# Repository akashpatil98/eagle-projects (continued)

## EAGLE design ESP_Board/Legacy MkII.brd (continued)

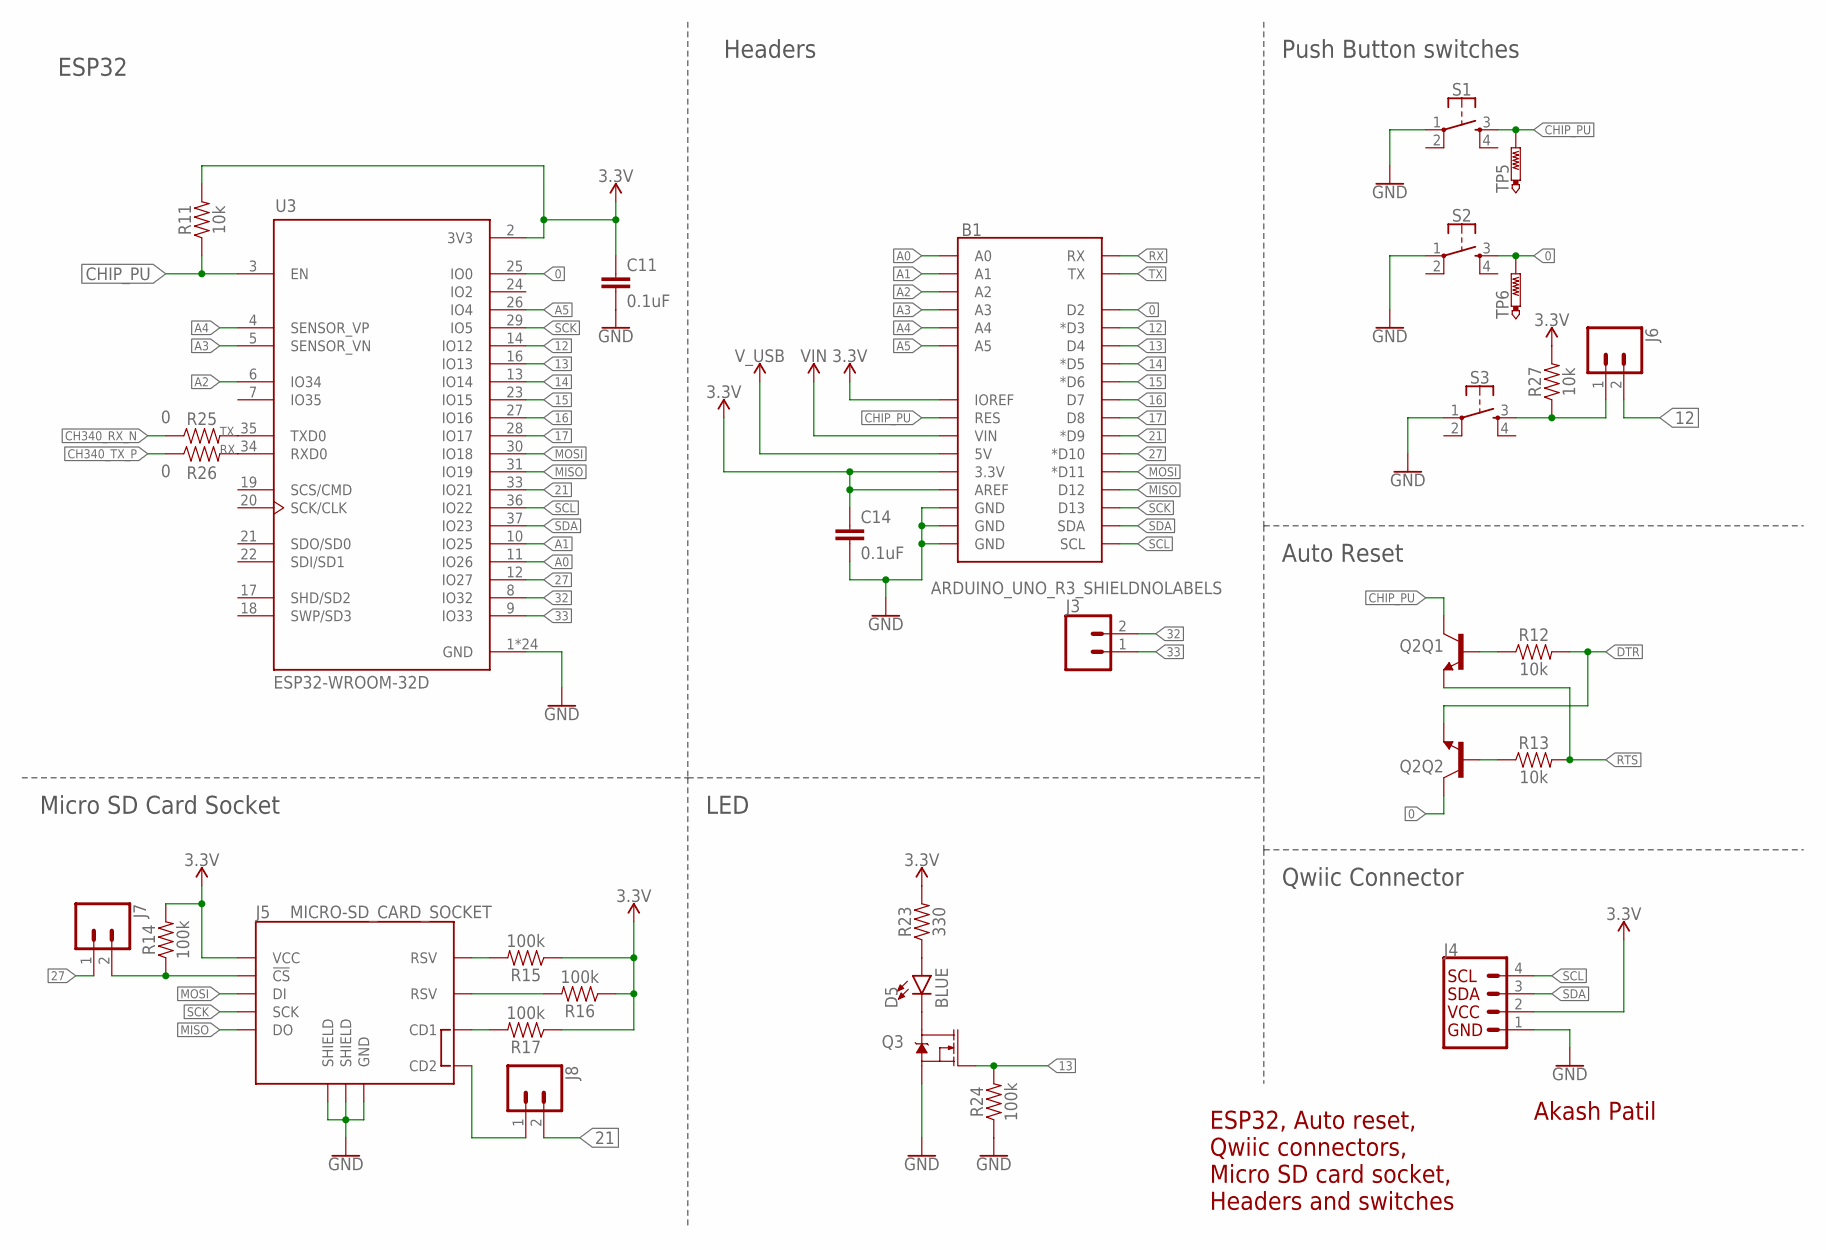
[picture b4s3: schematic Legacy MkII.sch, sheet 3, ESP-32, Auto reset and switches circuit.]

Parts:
B1: ARDUINO_UNO_R3_SHIELDNOLABELS; UNO_R3_SHIELD_NOLABELS
C11, C14: 0.1uF; 0603
D5: BLUE; LED-0603
J3: CONN_021X02_NO_SILK; 1X02_NO_SILK
J4: QWIIC_CONNECTORJS-1MM; 1X04_1MM_RA
J5: MICRO-SD_CARD_SOCKET; MICRO-SD-SOCKET
J6, J7, J8: CONN_02; 1X02
Q2: TRANS_NPN_DUAL-MBT3904DW1T1; SC70-6
Q3: 220mA/50V/3.5Ω; SOT23-3
R11, R12, R13, R27: 10k; 0603
R14, R15, R16, R17, R24: 100k; 0603
R23: 330; 0603
R25, R26: 0; 0603
S1, S2, S3: MOMENTARY-SWITCH-SPST-2-SMD-4.6X2.8MM; TACTILE_SWITCH_SMD_4.6X2.8MM
TP5, TP6: PTR1B1,27; B1,27
U3: ESP32-WROOM-32D; MODULE_ESP32-WROOM-32D

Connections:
0: B1.D2, Q2.6 (C), S2.3, TP6.TP, U3.25 (IO0)
3.3V: B1.3.3V, B1.AREF, B1.IOREF, C11.1, C14.1, J4.2 (VCC), J5.VCC, R11.2, R14.2, R15.1, R16.1, R17.1, R23.2, R27.2, U3.2 (3V3); also elsewhere on the board
12: B1.D3 (*D3), J6.2, U3.14 (IO12)
13: B1.D4, Q3.1 (G), R24.2, U3.16 (IO13)
14: B1.D5 (*D5), U3.13 (IO14)
15: B1.D6 (*D6), U3.23 (IO15)
16: B1.D7, U3.27 (IO16)
17: B1.D8, U3.28 (IO17)
21: B1.D9 (*D9), J8.2, U3.33 (IO21)
27: B1.D10 (*D10), J7.1, U3.12 (IO27)
32: J3.2, U3.8 (IO32)
33: J3.1, U3.9 (IO33)
A0: B1.A0, U3.11 (IO26)
A1: B1.A1, U3.10 (IO25)
A2: B1.A2, U3.6 (IO34)
A3: B1.A3, U3.5 (SENSOR_VN)
A4: B1.A4, U3.4 (SENSOR_VP)
A5: B1.A5, U3.26 (IO4)
CH340_RX_N: R25.1; also elsewhere on the board
CH340_TX_P: R26.1; also elsewhere on the board
CHIP_PU: B1.RES, Q2.3 (C), R11.1, S1.3, TP5.TP, U3.3 (EN)
DTR: Q2.1 (E), R12.2; also elsewhere on the board
GND: B1.GND@0 (GND), B1.GND@1 (GND), B1.GND@2 (GND), C11.2, C14.2, J4.1 (GND), J5.GND, J5.GND1 (SHIELD), J5.GND3 (SHIELD), Q3.2 (S), R24.1, S1.1, S2.1, S3.1, U3.1 (GND), U3.15 (GND), U3.38 (GND), U3.39_1 (GND), U3.39_2 (GND), U3.39_3 (GND), U3.39_4 (GND), U3.39_5 (GND), U3.39_6 (GND), U3.39_7 (GND), U3.39_8 (GND), U3.39_9 (GND), U3.39_10 (GND), U3.39_11 (GND), U3.39_12 (GND), U3.39_13 (GND), U3.39_14 (GND), U3.39_15 (GND), U3.39_16 (GND), U3.39_17 (GND), U3.39_18 (GND), U3.39_19 (GND), U3.39_20 (GND), U3.39_21 (GND); also elsewhere on the board
MISO: B1.D12, J5.DO, U3.31 (IO19)
MOSI: B1.D11 (*D11), J5.DI, U3.30 (IO18)
unnamed: J5.CD2, J8.1
unnamed: J5.CS (!CS), J7.2, R14.1
unnamed: D5.A, R23.1
unnamed: Q2.5 (B), R12.1
unnamed: Q2.2 (B), R13.1
unnamed: J5.RSV1 (RSV), R15.2
unnamed: D5.C, Q3.3 (D)
unnamed: J5.RSV2 (RSV), R16.2
unnamed: J5.CD1, R17.2
unnamed: J6.1, R27.1, S3.3
RTS: Q2.4 (E), R13.2; also elsewhere on the board
RX: B1.RX, R26.2, U3.34 (RXD0)
SCK: B1.D13, J5.SCLK (SCK), U3.29 (IO5)
SCL: B1.SCL, J4.4 (SCL), U3.36 (IO22)
SDA: B1.SDA, J4.3 (SDA), U3.37 (IO23)
TX: B1.TX, R25.2, U3.35 (TXD0)
VIN: B1.VIN; also elsewhere on the board
V_USB: B1.5V; also elsewhere on the board

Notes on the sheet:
Akash Patil
ESP32, Auto reset, Qwiic connectors, Micro SD card socket, Headers and switches
Auto Reset
Push Button switches
ESP32
LED
Qwiic Connector
Headers
Micro SD Card Socket

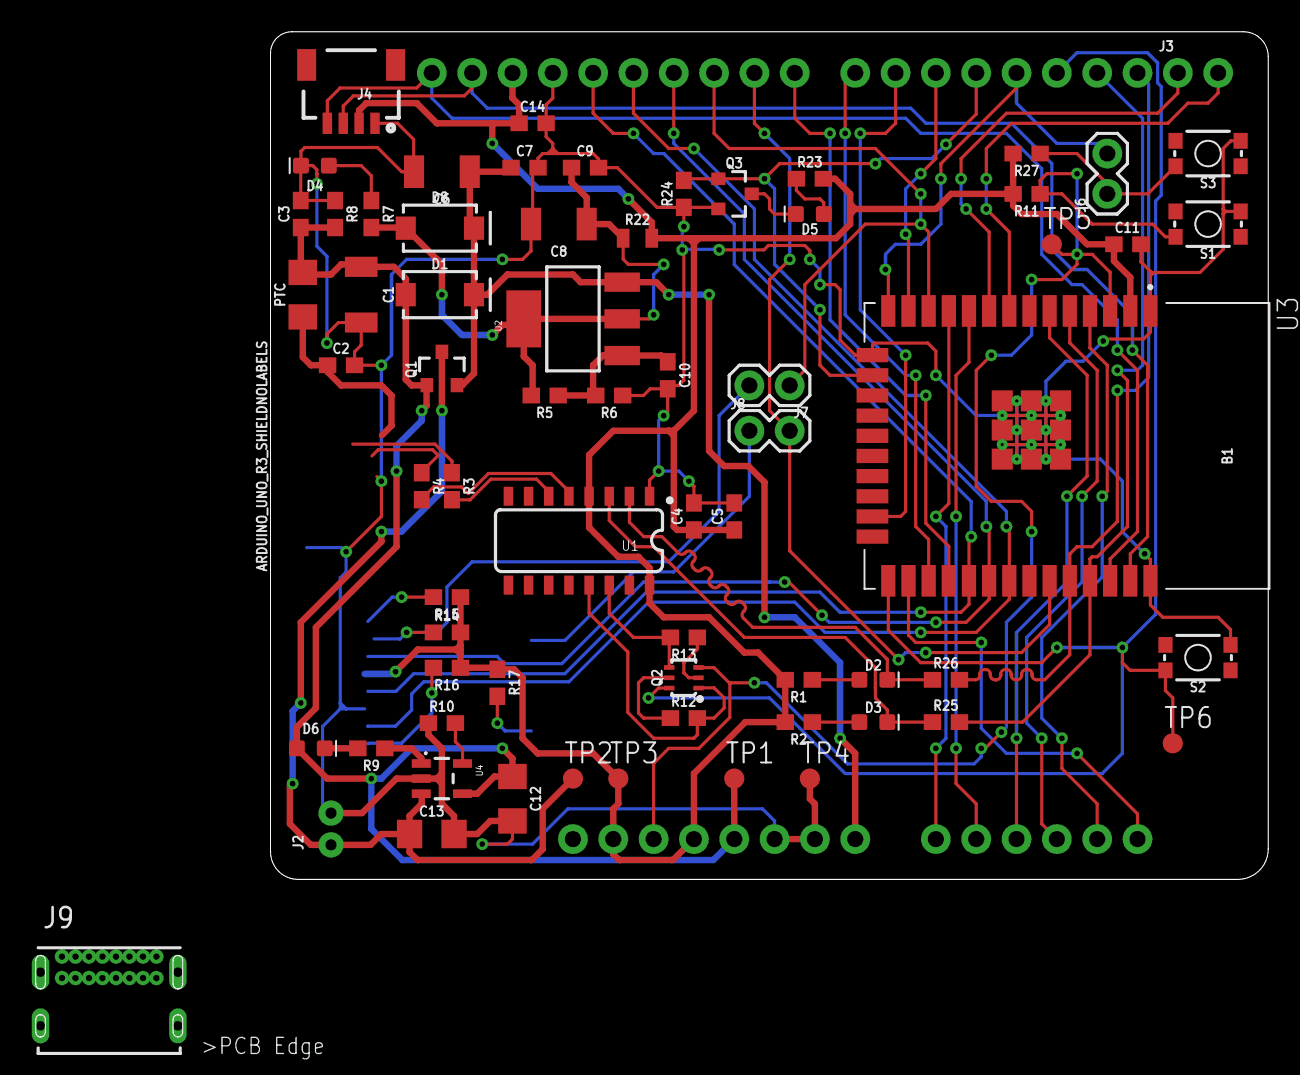
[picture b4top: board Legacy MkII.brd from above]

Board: 2 copper layers, 77.6 x 63.3 mm, 70 parts (1 on the bottom side), 58 nets.

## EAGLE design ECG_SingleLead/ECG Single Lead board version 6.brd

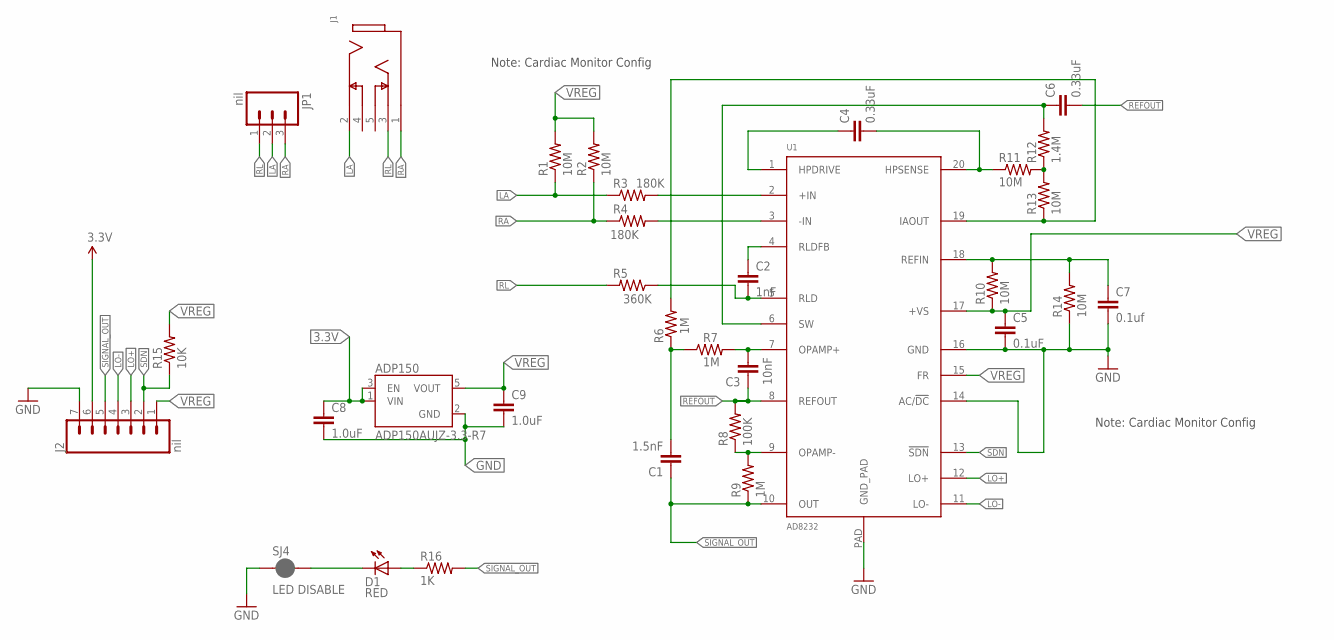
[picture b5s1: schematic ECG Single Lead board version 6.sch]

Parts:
ADP150: ADP150AUJZ-3.3-R7; SOT95P280X100-5N
C1: 1.5nF; 0603-CAP
C2: 1nF; 0603-CAP
C3: 10nF; 0603-CAP
C4, C6: 0.33uF; 0805
C5: 0.1uF; 0603-CAP
C7: 0.1uf; 0603-CAP
C8, C9: 1.0uF; 0603
D1: RED; LED-0603
J1: 35RASMT4BHNTRX; SWITCHCRAFT_35RASMT4BHNTRX
J2: nil; 1X07
JP1: nil; 1X03
R1, R2, R10, R11, R13, R14: 10M; 0603-RES
R3, R4: 180K; 0603-RES
R5: 360K; 0603-RES
R6, R7, R9: 1M; 0603-RES
R8: 100K; 0603-RES
R12: 1.4M; 0603-RES
R15: 10K; 0603-RES
R16: 1K; 0603-RES
SJ4: LED DISABLE; SMT-JUMPER_2_NC_PASTE_SILK
U1: AD8232; LFCSP_20

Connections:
3.3V: ADP150.1 (VIN), ADP150.3 (EN), C8.1, J2.6
GND: ADP150.2 (GND), C5.2, C7.2, C8.2, C9.2, J2.7, R14.1, SJ4.1, U1.14 (AC/!DC), U1.16 (GND), U1.PAD (GND_PAD)
LA: J1.2, JP1.2, R1.1, R3.1
LO+: J2.3, U1.12 (LO+)
LO-: J2.4, U1.11 (LO-)
unnamed: R3.2, U1.2 (+IN)
unnamed: R4.2, U1.3 (-IN)
unnamed: C3.2, R7.2, U1.7 (OPAMP+)
unnamed: C4.2, R11.1, U1.20 (HPSENSE)
unnamed: C7.1, R10.2, R14.2, U1.18 (REFIN)
unnamed: D1.A, R16.1
unnamed: R8.1, R9.2, U1.9 (OPAMP-)
unnamed: R6.2, R13.1, U1.19 (IAOUT)
unnamed: C1.2, R6.1, R7.1
unnamed: D1.C, SJ4.2
unnamed: C4.1, U1.1 (HPDRIVE)
unnamed: R11.2, R12.1, R13.2
unnamed: C6.1, R12.2, U1.6 (SW)
unnamed: C2.1, U1.4 (RLDFB)
unnamed: C2.2, R5.1, U1.5 (RLD)
RA: J1.1, JP1.3, R2.1, R4.1
REFOUT: C3.1, C6.2, R8.2, U1.8 (REFOUT)
RL: J1.3, JP1.1, R5.2
SDN: J2.2, R15.1, U1.13 (!SDN)
SIGNAL_OUT: C1.1, J2.5, R9.1, R16.2, U1.10 (OUT)
VREG: ADP150.5 (VOUT), C5.1, C9.1, J2.1, R1.2, R2.2, R10.1, R15.2, U1.15 (FR), U1.17 (+VS)

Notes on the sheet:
Note: Cardiac Monitor Config

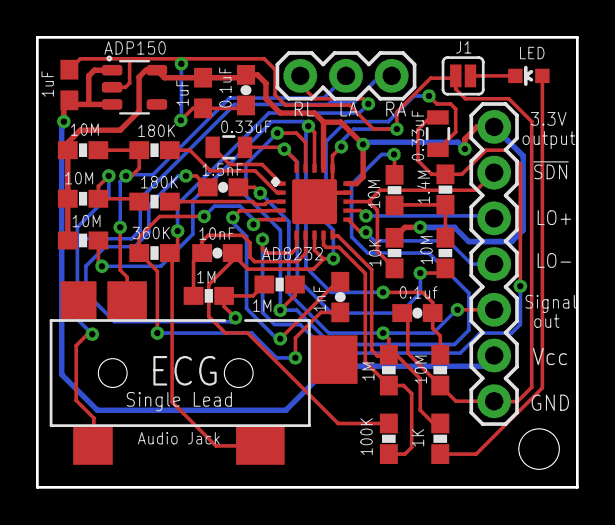
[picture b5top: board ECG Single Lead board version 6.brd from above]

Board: 2 copper layers, 30.0 x 25.0 mm, 32 parts (0 on the bottom side), 26 nets.

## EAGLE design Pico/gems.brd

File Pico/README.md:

## This folder contains the design files for Pico development kit

### The design was created using Autodesk Eagle.

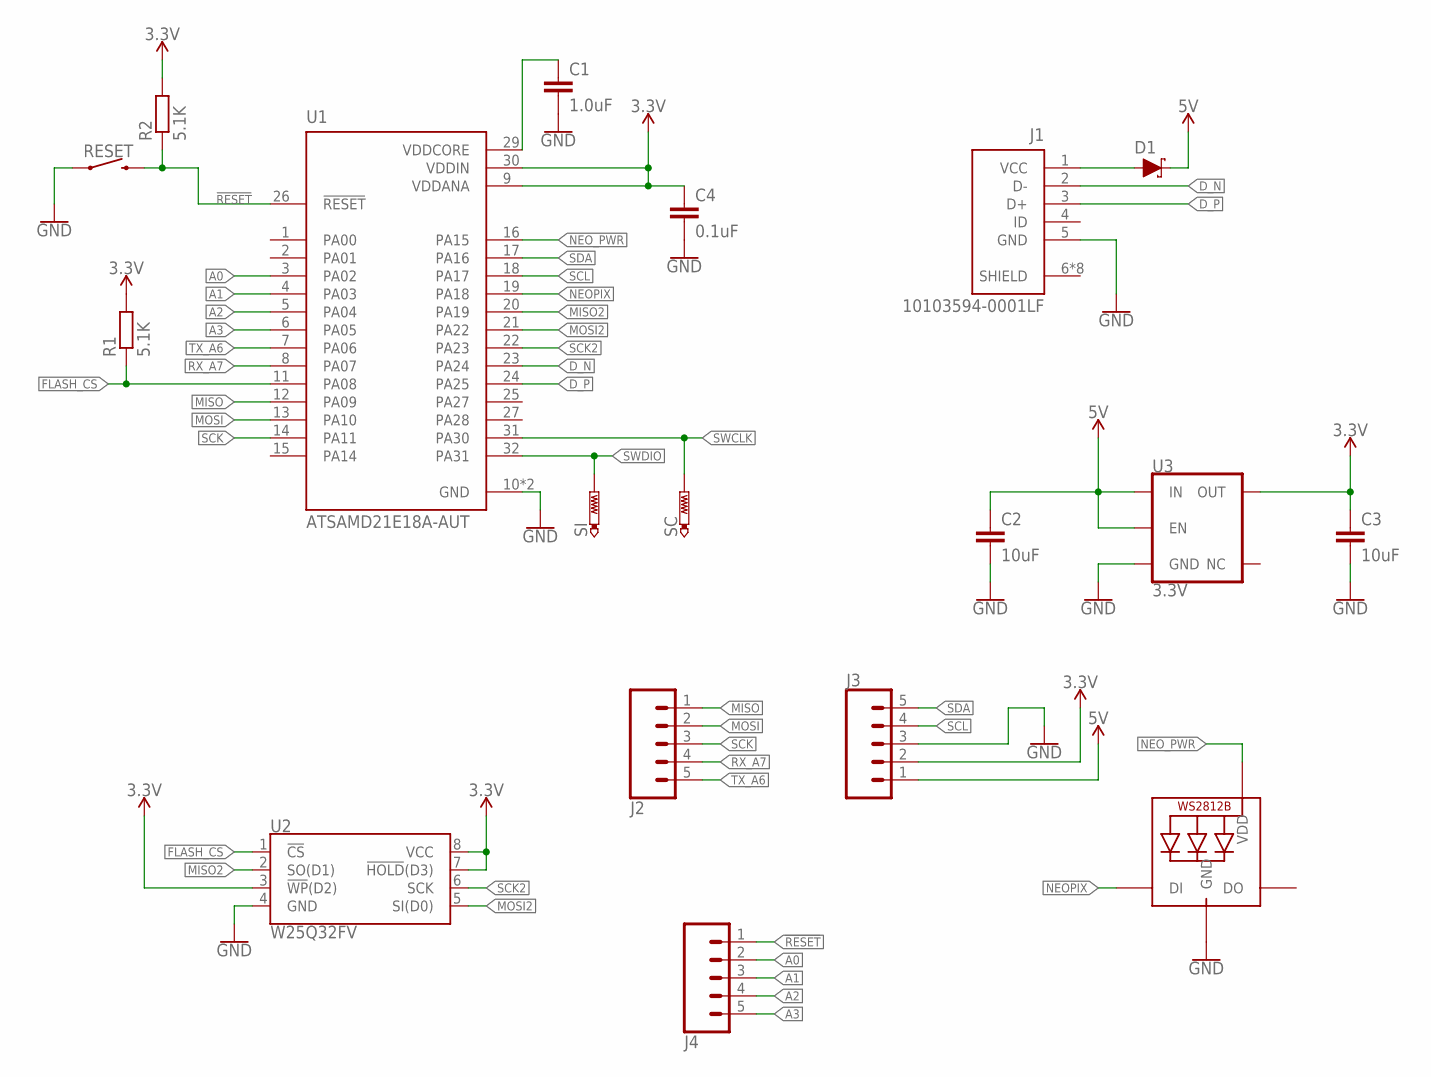
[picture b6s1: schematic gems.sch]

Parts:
C1: 1.0uF; 0402
C2, C3: 10uF; 0603
C4: 0.1uF; 0402
D1: 0.5A/40V/420mV; SOD-323
J1: 10103594-0001LF; AMPHENOL_10103594-0001LF
J2, J3, J4: CONN_05; 1X05
LED: WS2812B_SK6805_1515; SK6805_1515
R1, R2: 5.1K; R0402
RESET: MOMENTARY-SWITCH-SPST-SMD-4.6X2.8MM; TACTILE_SWITCH_SMD_4.6X2.8MM
SC: PTR1TP08R; TP08R
SI: PTR1TP08R; TP08R
U1: ATSAMD21E18A-AUT; QFP80P900X900X120-32N
U2: W25Q32FV; SOIC-8
U3: 3.3V; SOT23-5

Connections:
3.3V: C3.1, C4.1, J3.2, R1.2, R2.2, U1.9 (VDDANA), U1.30 (VDDIN), U2.3 (!WP!(D2)), U2.7 (!HOLD!(D3)), U2.8 (VCC), U3.5 (OUT)
5V: C2.1, D1.C, J3.1, U3.1 (IN), U3.3 (EN)
!RESET!: J4.1, R2.1, RESET.3 (2), RESET.4 (2), U1.26 (!RESET)
A0: J4.2, U1.3 (PA02)
A1: J4.3, U1.4 (PA03)
A2: J4.4, U1.5 (PA04)
A3: J4.5, U1.6 (PA05)
D_N: J1.2 (D-), U1.23 (PA24)
D_P: J1.3 (D+), U1.24 (PA25)
FLASH_CS: R1.1, U1.11 (PA08), U2.1 (!CS!)
GND: C1.2, C2.2, C3.2, C4.2, J1.5 (GND), J3.3, LED.4 (GND), RESET.1, RESET.2 (1), U1.10 (GND), U1.28 (GND), U2.4 (GND), U3.2 (GND)
MISO: J2.1, U1.12 (PA09)
MISO2: U1.20 (PA19), U2.2 (SO(D1))
MOSI: J2.2, U1.13 (PA10)
MOSI2: U1.21 (PA22), U2.5 (SI(D0))
unnamed: C1.1, U1.29 (VDDCORE)
unnamed: D1.A, J1.1 (VCC)
NEOPIX: LED.1 (DI), U1.19 (PA18)
NEO_PWR: LED.2 (VDD), U1.16 (PA15)
RX_A7: J2.4, U1.8 (PA07)
SCK: J2.3, U1.14 (PA11)
SCK2: U1.22 (PA23), U2.6 (SCK)
SCL: J3.4, U1.18 (PA17)
SDA: J3.5, U1.17 (PA16)
SWCLK: SC.TP, U1.31 (PA30)
SWDIO: SI.TP, U1.32 (PA31)
TX_A6: J2.5, U1.7 (PA06)

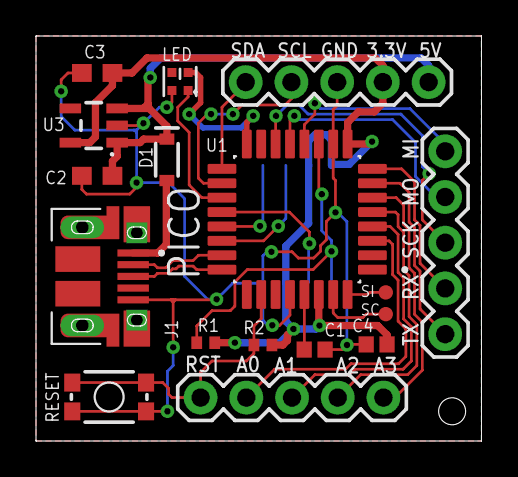
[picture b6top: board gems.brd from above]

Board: 2 copper layers, 24.8 x 22.5 mm, 18 parts (1 on the bottom side), 27 nets.

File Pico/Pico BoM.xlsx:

Qty | Value | MPN | Package | Parts | Description | Digikey PN | Loading
3 |  |  | 1X05 | J2, J3, J4 | Generic Header-pin footprint for 0.1 inch spaced/style header connections |  | DNP
1 | 0.1uF | CL05B104KP5NNNC | 0402 | C4 | CAP CER 0.1UF 10V X7R 0402 | 1276-1002-1-ND
1 | 0.5A/40V/420mV | PMEG3010BEA,115 | SOD-323 | D1 | DIODE SCHOTTKY 30V 1A SOD323 | 1727-5199-1-ND
1 | 1.0uF | CL05A105MP5NNNC | 0402 | C1 | CAP CER 1UF 10V X5R 0402 | 1276-1448-1-ND
1 | 10103594-0001LF | 10103594-0001LF | AMPHENOL_10103594-0001LF | J1 | CONN RCPT USB2.0 MICRO B SMD R/A | 609-4050-1-ND
2 | 10uF | LMK107BBJ106MALT | 0603 | C2, C3 | CAP CER 10UF 10V X5R 0603 | 587-3258-1-ND
1 | 3.3V | AP2112K-3.3TRG1 | SOT23-5 | U3 | IC REG LINEAR 3.3V 600MA SOT25 | AP2112K-3.3TRG1DICT-ND
2 | 5.1K | RMCF0402JT5K10 | 0402 | R1, R2 | RES 5.1K OHM 5% 1/16W 0402 | RMCF0402JT5K10CT-ND
1 | ATSAMD21E18A-AUT | ATSAMD21E18A-AUT | 32-TQFP | U1 | IC MCU 32BIT 256KB FLASH 32TQFP | ATSAMD21E18A-AUTCT-ND
1 | MOMENTARY-SWITCH-SPST-SMD-4.6X2.8MM | KMR221GLFS | TACTILE_SWITCH_SMD_4.6X2.8MM | RESET | SWITCH TACTILE SPST-NO 0.05A 32V | 401-1427-1-ND
1 | SK6805-E-J | 4492 | SK6805_1515 | LED | ADDRESS LED DISCRETE RGB 1=10 | 1528-4492-ND

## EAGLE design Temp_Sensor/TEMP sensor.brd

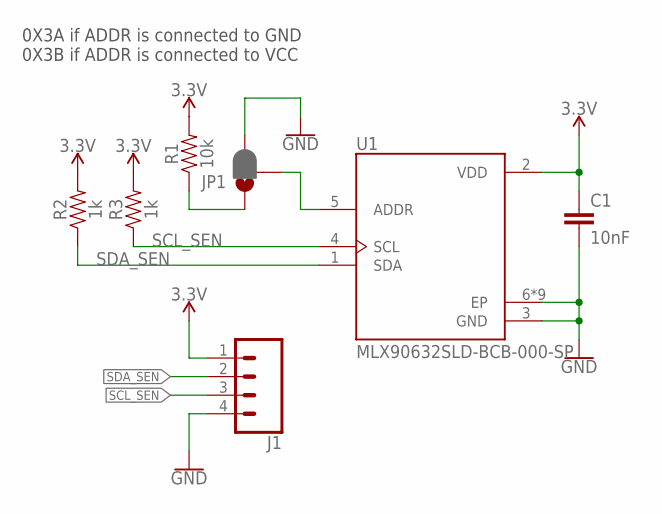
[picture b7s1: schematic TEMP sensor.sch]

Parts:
C1: 10nF; 0603
J1: CONN_04; 1X04
JP1: JUMPER-SMT_3_1-NC_PASTE_SILK; SMT-JUMPER_3_1-NC_PASTE_SILK
R1: 10k; 0603
R2, R3: 1k; 0603
U1: MLX90632SLD-BCB-000-SP; XDCR_MLX90632SLD-BCB-000-SP

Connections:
3.3V: C1.1, J1.1, R1.2, R2.2, R3.2, U1.2 (VDD)
GND: C1.2, J1.4, JP1.3, U1.3 (GND), U1.6 (EP), U1.P$1 (EP), U1.P$2 (EP), U1.P$3 (EP), U1.P$4 (EP), U1.P$5 (EP), U1.P$6 (EP), U1.P$7 (EP), U1.P$8 (EP)
unnamed: JP1.2, U1.5 (ADDR)
unnamed: JP1.1, R1.1
SCL_SEN: J1.3, R3.1, U1.4 (SCL)
SDA_SEN: J1.2, R2.1, U1.1 (SDA)

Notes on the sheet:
0X3A if ADDR is connected to GND 0X3B if ADDR is connected to VCC

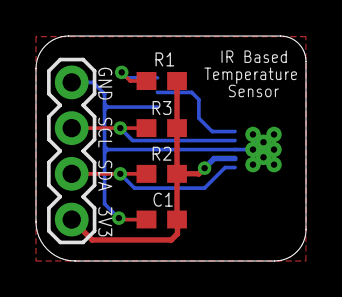
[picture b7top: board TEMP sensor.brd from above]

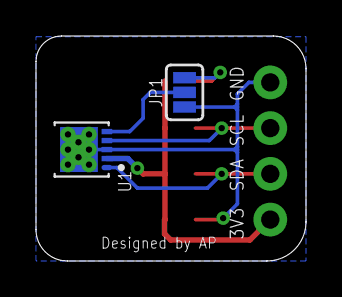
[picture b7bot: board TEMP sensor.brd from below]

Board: 2 copper layers, 15.0 x 12.5 mm, 7 parts (2 on the bottom side), 6 nets.

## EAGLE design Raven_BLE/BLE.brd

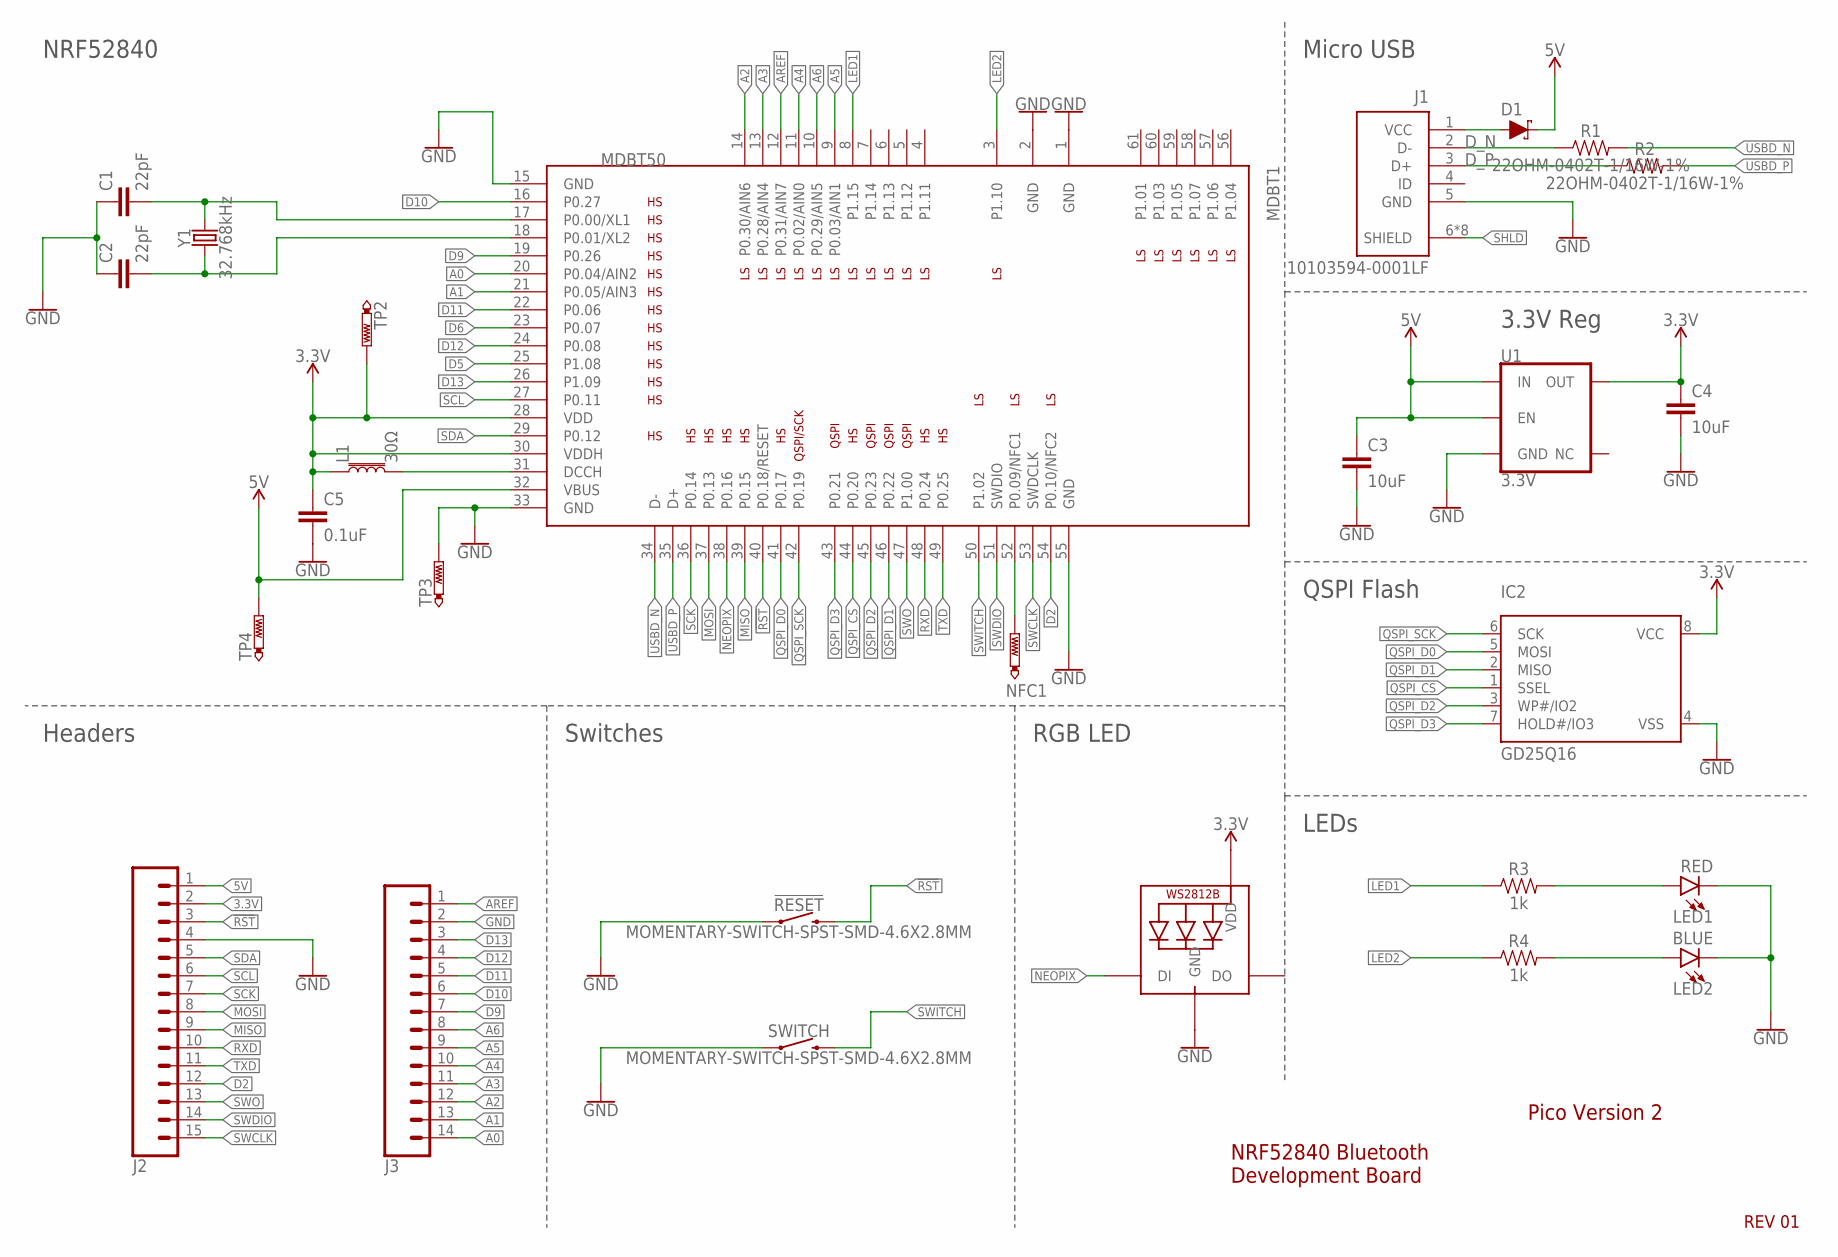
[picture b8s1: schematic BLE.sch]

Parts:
!RESET!: MOMENTARY-SWITCH-SPST-SMD-4.6X2.8MM; TACTILE_SWITCH_SMD_4.6X2.8MM
C1, C2: 22pF; 0402-TIGHT
C3, C4: 10uF; 0603
C5: 0.1uF; 0402-TIGHT
D1: 0.5A/40V/420mV; SOD-323
IC2: GD25Q16; USON8
J1: 10103594-0001LF; AMPHENOL_10103594-0001LF
J2: CONN_15; 1X15
J3: CONN_14; 1X14
L1: 30Ω; 0402-TIGHT
LED1: RED; LED-0603
LED2: BLUE; LED-0603
MDBT1: MDBT50
NFC1: PTR1TP10R; TP10R
R1, R2: 22OHM-0402T-1/16W-1%; 0402-TIGHT
R3, R4: 1k; 0402-TIGHT
RGB_LED: WS2812B_SK6805_1515; SK6805_1515
SWITCH: MOMENTARY-SWITCH-SPST-SMD-4.6X2.8MM; TACTILE_SWITCH_SMD_4.6X2.8MM
TP2, TP3, TP4: PTR1TP07R; TP07R
U1: 3.3V; SOT23-5
Y1: 32.768kHz; CRYSTAL-SMD-3.2X1.5MM

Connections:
3.3V: C4.1, C5.1, IC2.8 (VCC), J2.2, L1.1, MDBT1.28 (VDD), MDBT1.30 (VDDH), RGB_LED.2 (VDD), TP2.TP, U1.5 (OUT)
5V: C3.1, D1.C, J2.1, MDBT1.32 (VBUS), TP4.TP, U1.1 (IN), U1.3 (EN)
!RST!: !RESET!.3 (2), !RESET!.4 (2), J2.3, MDBT1.40 (P0.18/RESET)
A0: J3.14, MDBT1.20 (P0.04/AIN2)
A1: J3.13, MDBT1.21 (P0.05/AIN3)
A2: J3.12, MDBT1.14 (P0.30/AIN6)
A3: J3.11, MDBT1.13 (P0.28/AIN4)
A4: J3.10, MDBT1.11 (P0.02/AIN0)
A5: J3.9, MDBT1.9 (P0.03/AIN1)
A6: J3.8, MDBT1.10 (P0.29/AIN5)
AREF: J3.1, MDBT1.12 (P0.31/AIN7)
D2: J2.12, MDBT1.54 (P0.10/NFC2)
D5: MDBT1.25 (P1.08)
D6: MDBT1.23 (P0.07)
D9: J3.7, MDBT1.19 (P0.26)
D10: J3.6, MDBT1.16 (P0.27)
D11: J3.5, MDBT1.22 (P0.06)
D12: J3.4, MDBT1.24 (P0.08)
D13: J3.3, MDBT1.26 (P1.09)
D_N: J1.2 (D-), R1.1
D_P: J1.3 (D+), R2.1
GND: !RESET!.1, !RESET!.2 (1), C1.1, C2.1, C3.2, C4.2, C5.2, IC2.4 (VSS), J1.5 (GND), J2.4, J3.2, LED1.C, LED2.C, MDBT1.1 (GND), MDBT1.2 (GND), MDBT1.15 (GND), MDBT1.33 (GND), MDBT1.55 (GND), RGB_LED.4 (GND), SWITCH.1, SWITCH.2 (1), TP3.TP, U1.2 (GND)
LED1: MDBT1.8 (P1.15), R3.1
LED2: MDBT1.3 (P1.10), R4.1
MISO: J2.9, MDBT1.39 (P0.15)
MOSI: J2.8, MDBT1.37 (P0.13)
unnamed: C1.2, MDBT1.17 (P0.00/XL1), Y1.P$2 (2)
unnamed: C2.2, MDBT1.18 (P0.01/XL2), Y1.P$1 (1)
unnamed: D1.A, J1.1 (VCC)
unnamed: MDBT1.52 (P0.09/NFC1), NFC1.TP
unnamed: L1.2, MDBT1.31 (DCCH)
unnamed: LED1.A, R3.2
unnamed: LED2.A, R4.2
NEOPIX: MDBT1.38 (P0.16), RGB_LED.1 (DI)
QSPI_CS: IC2.1 (SSEL), MDBT1.44 (P0.20)
QSPI_D0: IC2.5 (MOSI), MDBT1.41 (P0.17)
QSPI_D1: IC2.2 (MISO), MDBT1.46 (P0.22)
QSPI_D2: IC2.3 (WP#/IO2), MDBT1.45 (P0.23)
QSPI_D3: IC2.7 (HOLD#/IO3), MDBT1.43 (P0.21)
QSPI_SCK: IC2.6 (SCK), MDBT1.42 (P0.19)
RXD: J2.10, MDBT1.48 (P0.24)
SCK: J2.7, MDBT1.36 (P0.14)
SCL: J2.6, MDBT1.27 (P0.11)
SDA: J2.5, MDBT1.29 (P0.12)
SHLD: J1.6 (SHIELD), J1.7 (SHIELD), J1.8 (SHIELD), J1.9 (SHIELD), J1.10 (SHIELD), J1.11 (SHIELD), J1.S1 (SHIELD), J1.S2 (SHIELD)
SWCLK: J2.15, MDBT1.53 (SWDCLK)
SWDIO: J2.14, MDBT1.51 (SWDIO)
SWITCH: MDBT1.50 (P1.02), SWITCH.3 (2), SWITCH.4 (2)
SWO: J2.13, MDBT1.47 (P1.00)
TXD: J2.11, MDBT1.49 (P0.25)
USBD_N: MDBT1.34 (D-), R1.2
USBD_P: MDBT1.35 (D+), R2.2

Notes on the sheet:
NRF52840
Headers
Switches
RGB LED
LEDs
QSPI Flash
3.3V Reg
Micro USB
REV 01
NRF52840 Bluetooth Development Board
Pico Version 2

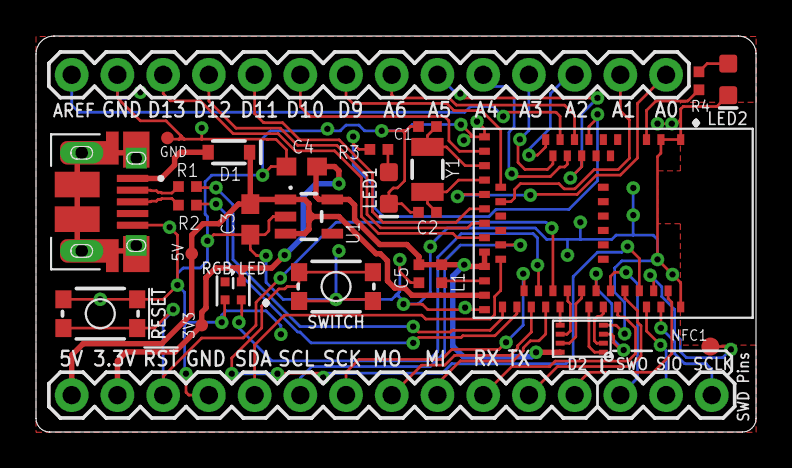
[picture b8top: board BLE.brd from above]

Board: 2 copper layers, 40.0 x 22.0 mm, 27 parts (0 on the bottom side), 50 nets.

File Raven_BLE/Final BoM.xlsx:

Column1 | Column2 | Column3 | Column4 | Column5 | Column6 | Column7
Part | Value | Device | Package | Description | Element14 | Digikey
!RESET! | MOMENTARY-SWITCH-SPST-SMD-4.6X2.8MM | MOMENTARY-SWITCH-SPST-SMD-4.6X2.8MM | TACTILE_SWITCH_SMD_4.6X2.8MM | Momentary Switch (Pushbutton) - SPST | Y
C1 | TBD (Load cap) | 22PF-0402T-16V-10% | 0402-TIGHT | Load caps for WCO | Y
C2 | TBD (Load cap) | 22PF-0402T-16V-10% | 0402-TIGHT | Load caps for WCO | Y
C3 | 10uF | 10UF-0603-6.3V-20% | 0603 | 10.0ÂµF ceramic capacitors | Y
C4 | 10uF | 10UF-0603-6.3V-20% | 0603 | 10.0ÂµF ceramic capacitors | Y
C5 | 0.1uF | 0.1UF-0402T-10V-10%-X7R | 0402-TIGHT | 0.1ÂµF ceramic capacitors | Y
D1 | 0.5A/40V/420mV | DIODE-SCHOTTKY-PMEG4005EJ | SOD-323 | Schottky diode | Y
IC2 | GD25Q16 | SPIFLASH_8PINUX | USON8 | SOIC8 SPI Flash
J1 | 10103594-0001LF | 10103594-0001LF | AMPHENOL_10103594-0001LF | USB - micro B USB 2.0 Receptacle Connector 5 Position Surface Mount, Right Angl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 | Y
LED1 | RED | LED-RED0603 | LED-0603 | Red SMD LED | Y
LED2 | BLUE | LED-BLUE0603 | LED-0603 | Blue SMD LED | Y
Module | MDBT50Q | MDBT50Q | MDBT50 | Raytac Corporation
R1 | 22OHM-0402T-1/16W-1% | 22OHM-0402T-1/16W-1% | 0402-TIGHT | 22Î© resistor | Y
R2 | 22OHM-0402T-1/16W-1% | 22OHM-0402T-1/16W-1% | 0402-TIGHT | 22Î© resistor | Y
R3 | 1k | 1KOHM-0402T-1/16W-1% | 0402-TIGHT | 1kÎ© resistor | Y
R4 | 1k | 1KOHM-0402T-1/16W-1% | 0402-TIGHT | 1kÎ© resistor | Y
RGB_LED | WS2812B_SK6805_1515 | WS2812B_SK6805_1515 | SK6805_1515 |  |  | Y
SWITCH | MOMENTARY-SWITCH-SPST-SMD-4.6X2.8MM | MOMENTARY-SWITCH-SPST-SMD-4.6X2.8MM | TACTILE_SWITCH_SMD_4.6X2.8MM | Momentary Switch (Pushbutton) - SPST | Y
U1 | 3.3V | V_REG_AP2112K-3.3V | SOT23-5 | AP2112 - 600mA CMOS LDO Regulator w/ Enable | Y
Y1 | 32.768kHz | CRYSTAL-32.768KHZSMD-3.2X1.5 | CRYSTAL-SMD-3.2X1.5MM | 32.768kHz Crystal | Y

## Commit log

2021-06-10 Changing from MIT license to GLGP LICENSE
2021-11-01 Create LICENSE
